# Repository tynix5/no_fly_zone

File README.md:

# no_fly_zone
A custom designed quadcopter and remote combination featuring a custom STM32-based flight controller PCB and STM32-based remote control PCB that combine aspects of sensor fusion, quaternion-based attitude control, wireless communication, and digital ESC communication.

<p align="center">
  <br>
  <em>Fully-assembled quadcopter</em>
</p>

<p align="center">
  <br>
  <em>Flight controller pictured with ESC mounted underneath</em>
</p>

<p align="center">
  <br>
  <em>Custom flight controller PCB</em>
</p>

<p align="center">
  <br>
  <em>Custom remote control frame</em>
</p>

<p align="center">
  <br>
  <em>Remote control PCB</em>
</p>

## Overview
This project focused on the design and implementation of a custom quadcopter flight controller paired with a complementary custom remote from the ground-up. Rather than buying an off-the-shelf flight controller and remote, almost all aspects of both the flight controller and remote were custom made. I decided to do this project because I have always been fascinated by drones, and I liked the challenge it would bring. It ties together all aspects of signal integrity, systems, low-level firmware, and digital signal processing. Below is a summary of some of the aspects this project entailed...

### Custom Features
- Flight controller PCB
- Remote control PCB
- Remote control frame
- Sensor fusion firmware
- Wireless nRF24L01 driver and handler
- Digital ESC communication implementation (DShot)
- Sensor libraries (IMU, Barometer, etc.)
- Encoder and OLED display libraries for remote control

No off-the-shelf software or firmware was used, but some aspects of flight controller design were inspired by PixHawk and Betaflight. Components purchased off-shelf include the ESC, four BLDC motors, quadcopter frame, and board components.

## Folder Overview
### /firmware
Contains source code, build settings, documentation, and additional information/diagrams for both the remote and quadcopter. A link to the STM32 submodule library can also be found, where most of the sensor implementation is found.

Note: The scripts subfolder in /firmware contains AI-generated Python scripts for validation and testing purposes. AI was NOT used to generate code found on either the remote or flight controller.

### /hardware
Contains KiCAD schematics and and PCB fabrication outputs for both the remote and quadcopter. Additional information on hardware selection and design can be found in each respective subfolder.

### /3d
Contains the 3D files for the spacers used to separate the STM32 flight controller board and ESC board, along with the 3D files for the remote control housing.

### /screenshots
Contains relevant screenshots for those in other READMEs

## BOM
All components purchased off-shelf can be found in the `bom.txt` file, and the BOMs for the PCBs can be found in the `.csv` files in their respective folders.

## Improvements
- Use of magnetometer or GPS unit for absolute heading
- Use of barometer for altitude hold
- Improved remote control PCB including nonvolatile storage (for PID parameters) and amplified transmission power
- Newer remote frame design

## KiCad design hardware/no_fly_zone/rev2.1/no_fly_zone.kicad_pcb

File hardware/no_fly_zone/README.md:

# no_fly_zone Schematic + PCB
## Overview

<p align="center">
  <br>
  <em>Flight controller PCBs. From left to right: Revision 1.0, 2.0, 2.1</em>
</p>

### Microcontroller
The MCU chosen was the STM32F446RCT for its high maximum clock frequency, dedicated FPU (for quaternion calculations), and abundant peripherals (SPI, timers, etc.). 
### IMU/Sensor Suite
The sensor suite in Revision 1.0 consists of a 6DOF IMU, magnetometer, barometer, and GPS. The IMU provides information on pitch and roll, magnetometer on yaw, barometer on altitude, and GPS for extended yaw support as well as location tracking for future revisions. Onboard magnetometers are very susceptible to EMF fields from motors, other sensors, as well as PCB traces. Thus, the GPS can be used as a backup for heading. Each subsequent iteration of the PCB reduced the sensors complexity until only the IMU and (optional) barometer remained. The GPS was removed for size and complexity reasons, and the magnetometer was removed due to the reasons described above. 
### Radio Communication
The nRF24L01 was the chosen RF link between the flight controller and remote for availablity and simplicity of implementation. In the future, a dedicated PA + LNA chip may be added on board to extend quadcopter range.
### Power Regulation
The power regulation circuit regulates the battery voltage (~16.8V) down to a smooth 5V, using a buck converter, then down to 3.3V, using an LDO, for powering the flight controller.

## Revision 1.0
### Summary

The single schematic given here is separated into two boards. A singular board containing all components was not able to fit onto the quadcopter frame. Thus, a separate MCU board and sensor board were produced using KiKit and connectors were used to share power and communication.

### Schematics

#### Hierarchal Schematic
The hierarchal schematic provides a top-level overview of the two boards. The ESC connectors, power schematic, and RF schematic were all included on the MCU board. The sensor board contains only the sensor schematic.

#### MCU

#### Sensors

#### Power

#### RF
Like the RF section on the remote, the nRF24L01 is surrounded by a continuous ground plane on the top layer as well as the layer directly underneath the antenna for stability. Stitching vias are placed about ~6mm apart (between lambda/10 - lambda/20 of 2.4 GHz wavelength) near antenna for shielding.

#### Misc
Contains 8 M3 screw holes, 4 for each board. Not shown for brevity.

#### PCB

#### 3D

## Revision 2.0
### Summary 
This revision involved consolidating the sensor board and MCU and removing the onboard magnetometer and GPS. The goal of this project was to achieve simple flight manuevers and hovering, and using these sensors would require more in depth sensor fusion algorithms. The antenna section was improved with further RF shielding and stitching vias, as well as a taper from the RF unbalanced port to the SMA pad. The board stackup changed from SIG - GND - 3.3V - SIG to a SIG - GND - GND - SIG + 3.3V to reduce buck converter and RF noise. 

Revision 1.0 board worked, but there were some problems with the JST connectors, making it hard to keep communication with the sensors, and they would not have been very reliable in a noisy and harsh environment. Ground lines were needed next to every signal line, but only one ground line was used on the entire board (power connector).

### Changes
- Consolidated sensor and controller board
- Removed magnetometer and GPS
- Improved RF shielding and layout
- Layer stackup changed from SIG-GND-3.3V-SIG to SIG-GND-GND-3.3V

### Schematics

### Hierarchal Schematic

#### MCU

#### Sensors

#### Power

#### RF

#### PCB

#### 3D

## Revision 2.1

### Summary 
While working with the Revision 2.0 flight controller, it was too large to fit comfortably on the quadcopter frame, so changes were made to reduce size while keeping functionality

### Changes
- Board size reduced from 50mm x 50mm to 40mm x 40mm
- Most part footprints reduced from 0805 packages to 0603
- Added TVS diodes to power inputs and connectors
- Removed ferrite bead in series with RF power supply
- Changed debug connector to STLINK specific
- Moved STAT3 from PB2 to PB8

#### MCU

#### Sensors

#### Power

#### RF

#### 3D

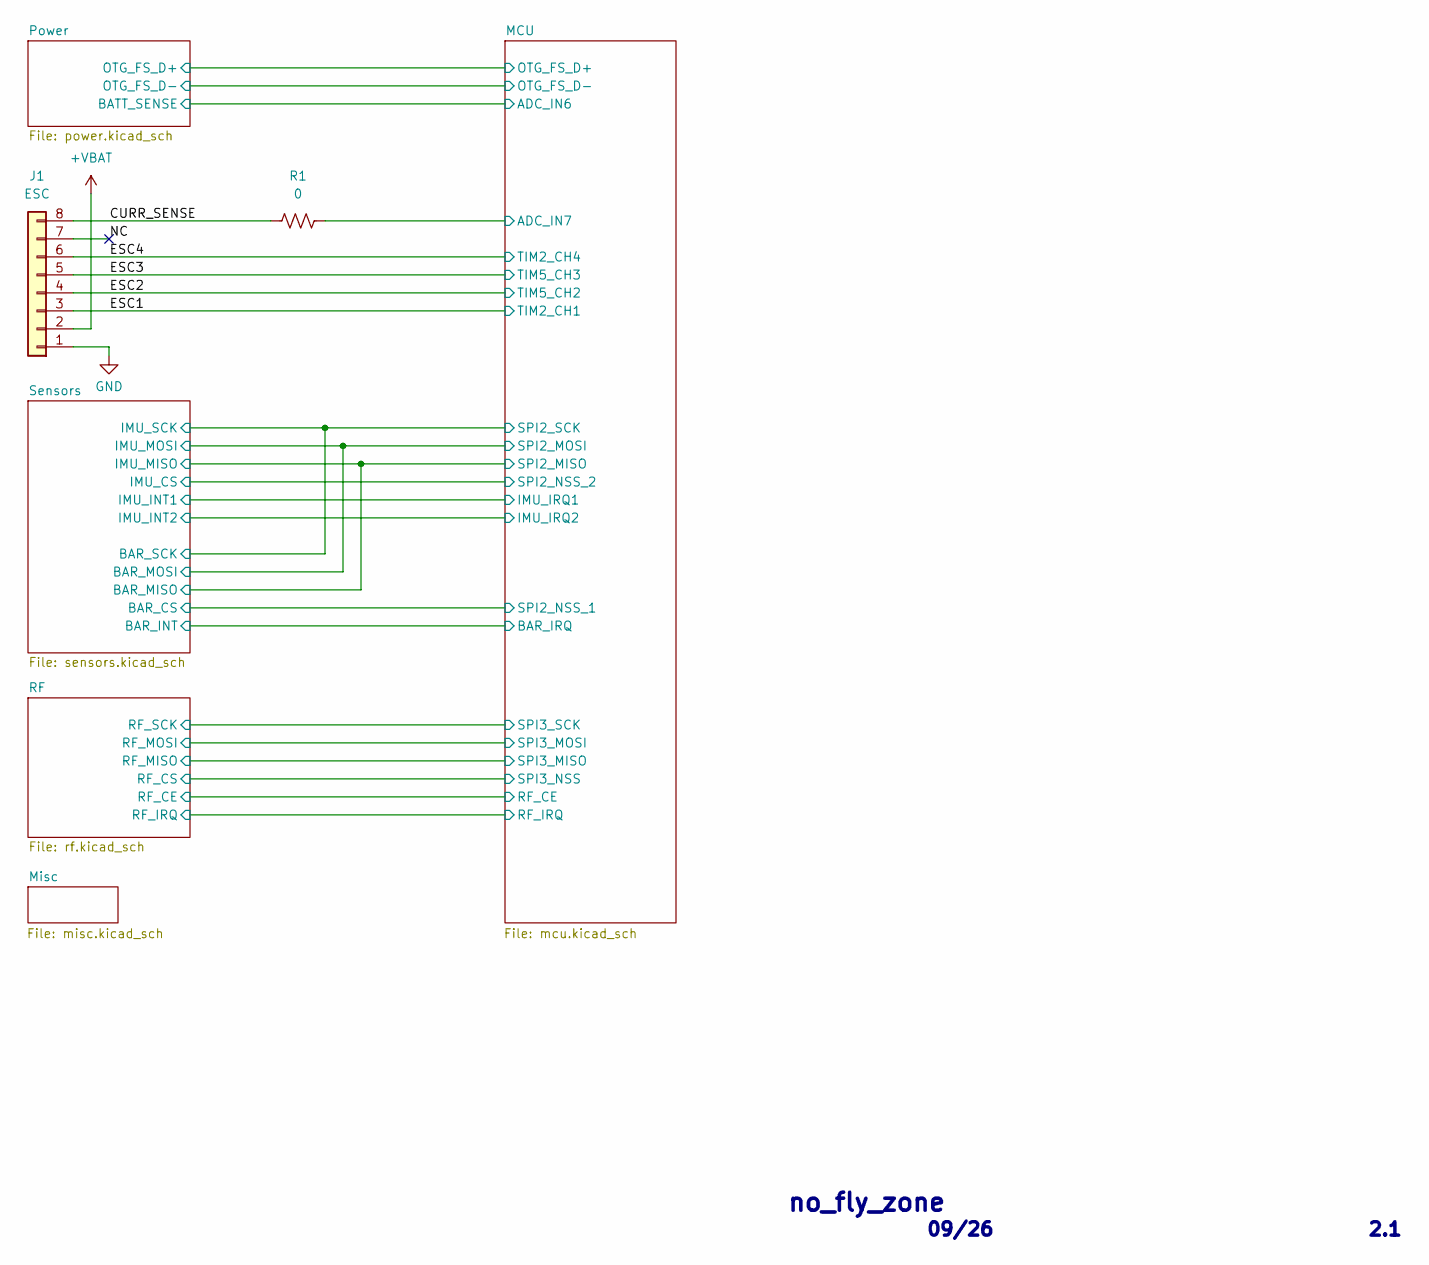
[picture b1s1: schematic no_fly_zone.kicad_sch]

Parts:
J1: ESC; JST_SH_SM08B-SRSS-TB_1x08-1MP_P1.00mm_Horizontal
R1: 0; R_0603_1608Metric

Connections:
+VBAT: J1.2; also elsewhere on the board
/CURR_SENSE: J1.8, R1.1
/ESC1: J1.3; also elsewhere on the board
/ESC2: J1.4; also elsewhere on the board
/ESC3: J1.5; also elsewhere on the board
/ESC4: J1.6; also elsewhere on the board
/MCU/ADC_IN7: R1.2; also elsewhere on the board
/NC: J1.7
GND: J1.1; also elsewhere on the board

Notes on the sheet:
no_fly_zone
2.1
09/26

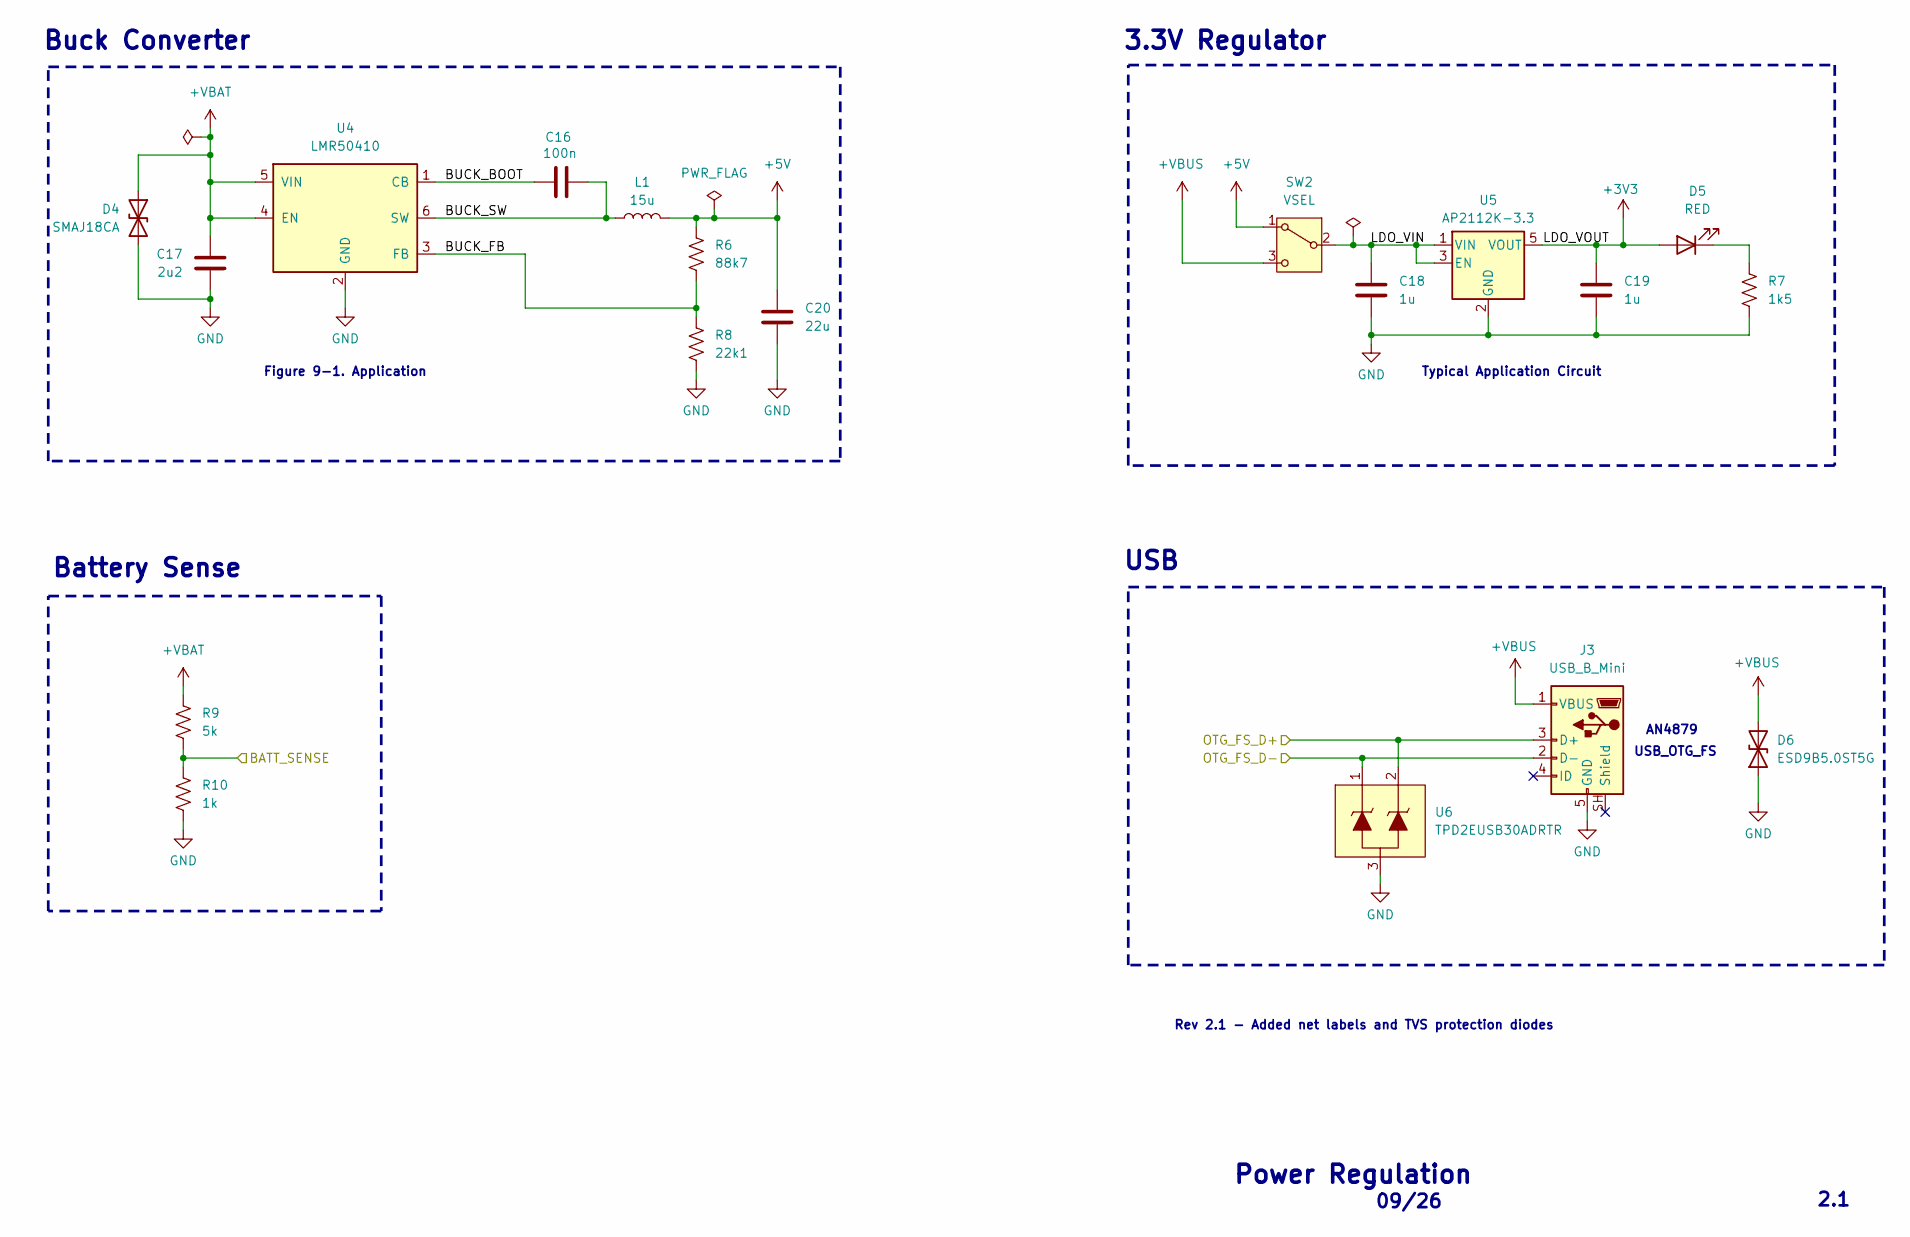
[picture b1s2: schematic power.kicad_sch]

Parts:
C16: 100n; C_0603_1608Metric
C17: 2u2; C_0603_1608Metric
C18, C19: 1u; C_0603_1608Metric
C20: 22u; C_0805_2012Metric
D4: SMAJ18CA; D_SMA
D5: RED; LED_0603_1608Metric
D6: ESD9B5.0ST5G; D_SOD-923
J3: USB_B_Mini; EDAC_690-005-299-043
L1: 15u; L_0805_2012Metric
R6: 88k7; R_0805_2012Metric
R7: 1k5; R_0603_1608Metric
R8: 22k1; R_0805_2012Metric
R9: 5k; R_0805_2012Metric
R10: 1k; R_0805_2012Metric
SW2: VSEL; SW_SPDT_PCM12
U4: LMR50410; SOT-23-6
U5: AP2112K-3.3; SOT-23-5
U6: SOT-723

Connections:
+3V3: C19.1, D5.2 (A), U5.5 (VOUT); also elsewhere on the board
+5V: C20.1, L1.2, R6.1, SW2.1 (A)
+VBAT: C17.1, D4.1 (A1), R9.1, U4.4 (EN), U4.5 (VIN); also elsewhere on the board
+VBUS: D6.2 (A2), J3.1 (VBUS), SW2.3 (C)
/MCU/ADC_IN6: R9.2, R10.1; also elsewhere on the board
/MCU/OTG_FS_D+: J3.3 (D+), U6.2; also elsewhere on the board
/MCU/OTG_FS_D-: J3.2 (D-), U6.1; also elsewhere on the board
/Power/BUCK_BOOT: C16.1, U4.1 (CB)
/Power/BUCK_FB: R6.2, R8.1, U4.3 (FB)
/Power/BUCK_SW: C16.2, L1.1, U4.6 (SW)
/Power/LDO_VIN: C18.1, SW2.2 (B), U5.1 (VIN), U5.3 (EN)
GND: C17.2, C18.2, C19.2, C20.2, D4.2 (A2), D6.1 (A1), J3.5 (GND), R7.2, R8.2, R10.2, U4.2 (GND), U5.2 (GND), U6.3; also elsewhere on the board
unnamed: D5.1 (K), R7.1

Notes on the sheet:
USB
Figure 9-1. Application
USB_OTG_FS
09/26
AN4879
Buck Converter
Power Regulation
3.3V Regulator
Rev 2.1 - Added net labels and TVS protection diodes
2.1
Battery Sense
Typical Application Circuit

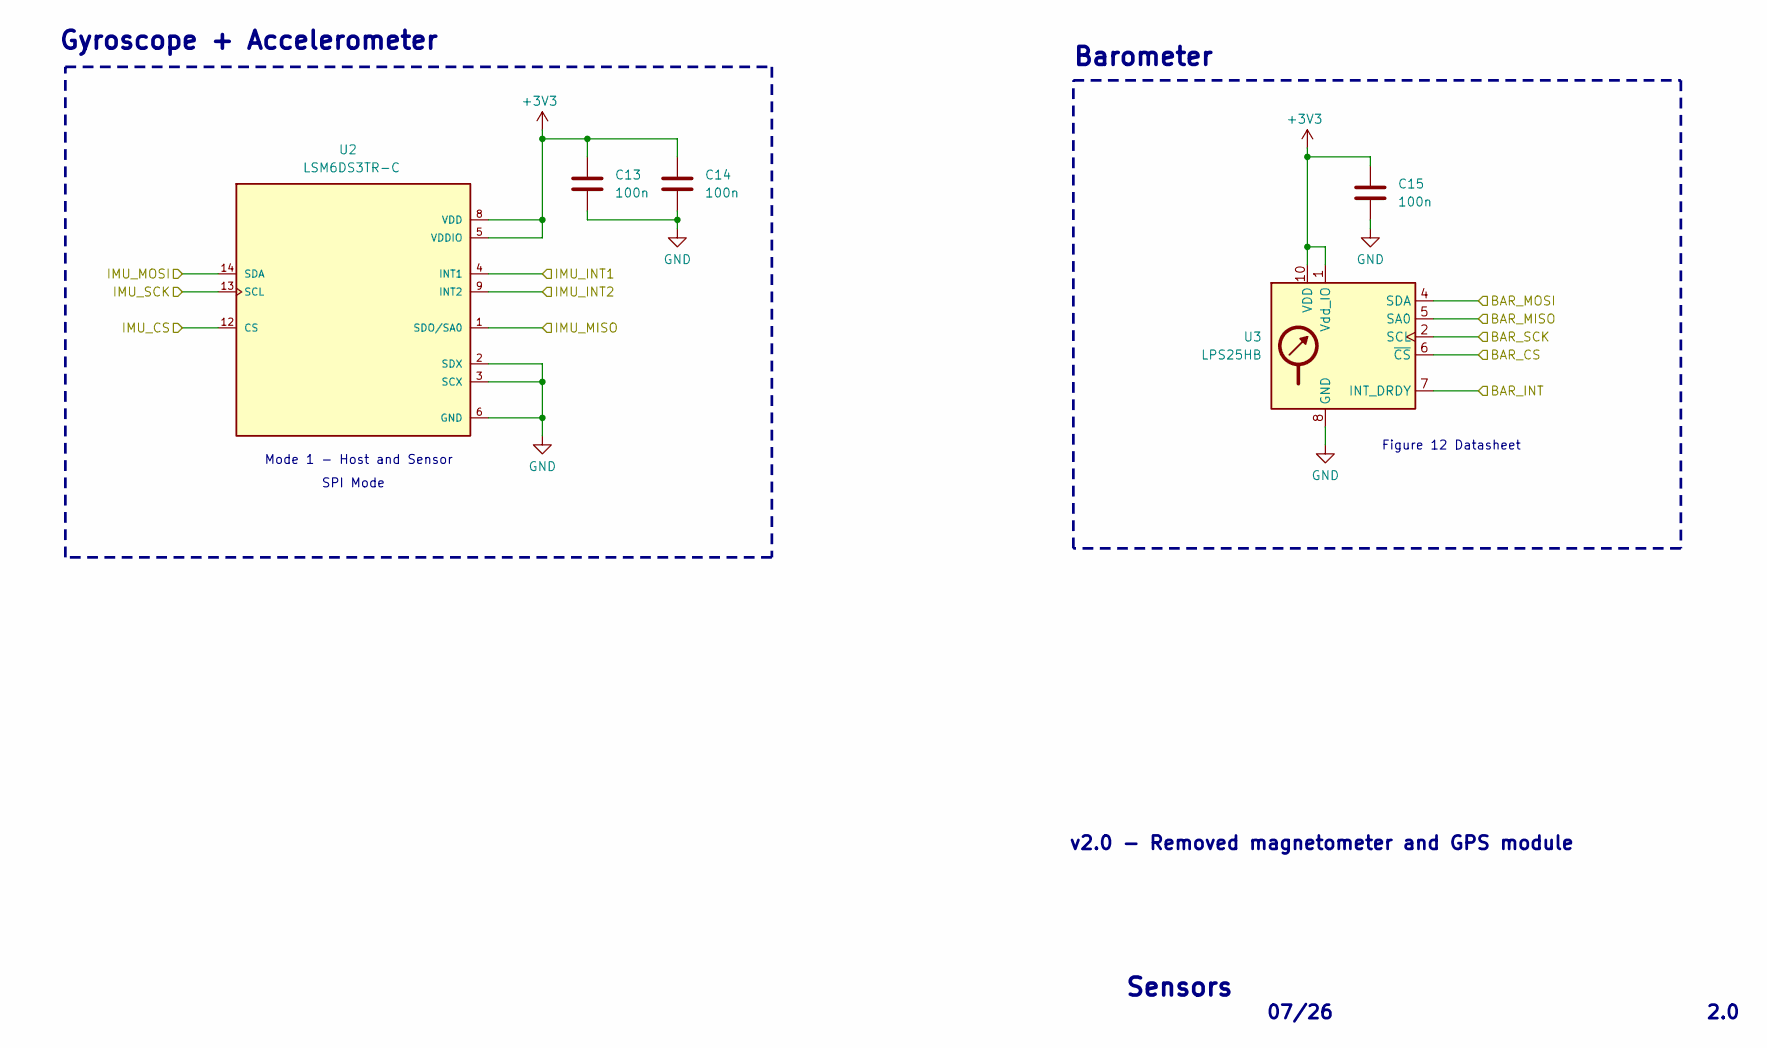
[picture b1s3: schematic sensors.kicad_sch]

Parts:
C13, C14, C15: 100n; C_0603_1608Metric
U2: LSM6DS3TR-C; LSM6DS3TR
U3: LPS25HB; ST_HLGA-10_2.5x2.5mm_P0.6mm_LayoutBorder3x2y

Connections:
+3V3: C13.1, C14.1, C15.1, U2.5 (VDDIO), U2.8 (VDD), U3.1 (Vdd_IO), U3.10 (VDD); also elsewhere on the board
/MCU/BAR_IRQ: U3.7 (INT_DRDY); also elsewhere on the board
/MCU/IMU_IRQ1: U2.4 (INT1); also elsewhere on the board
/MCU/IMU_IRQ2: U2.9 (INT2); also elsewhere on the board
/MCU/SPI2_MISO: U2.1 (SDO/SA0), U3.5 (SA0); also elsewhere on the board
/MCU/SPI2_MOSI: U2.14 (SDA), U3.4 (SDA); also elsewhere on the board
/MCU/SPI2_NSS_1: U3.6 (~CS); also elsewhere on the board
/MCU/SPI2_NSS_2: U2.12 (CS); also elsewhere on the board
/MCU/SPI2_SCK: U2.13 (SCL), U3.2 (SCL); also elsewhere on the board
GND: C13.2, C14.2, C15.2, U2.2 (SDX), U2.3 (SCX), U2.6 (GND), U2.7 (GND), U3.3 (GND), U3.8 (GND), U3.9 (GND); also elsewhere on the board

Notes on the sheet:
SPI Mode
Barometer
07/26
Mode 1 - Host and Sensor
2.0
Gyroscope + Accelerometer
Figure 12 Datasheet
v2.0 - Removed magnetometer and GPS module
Sensors

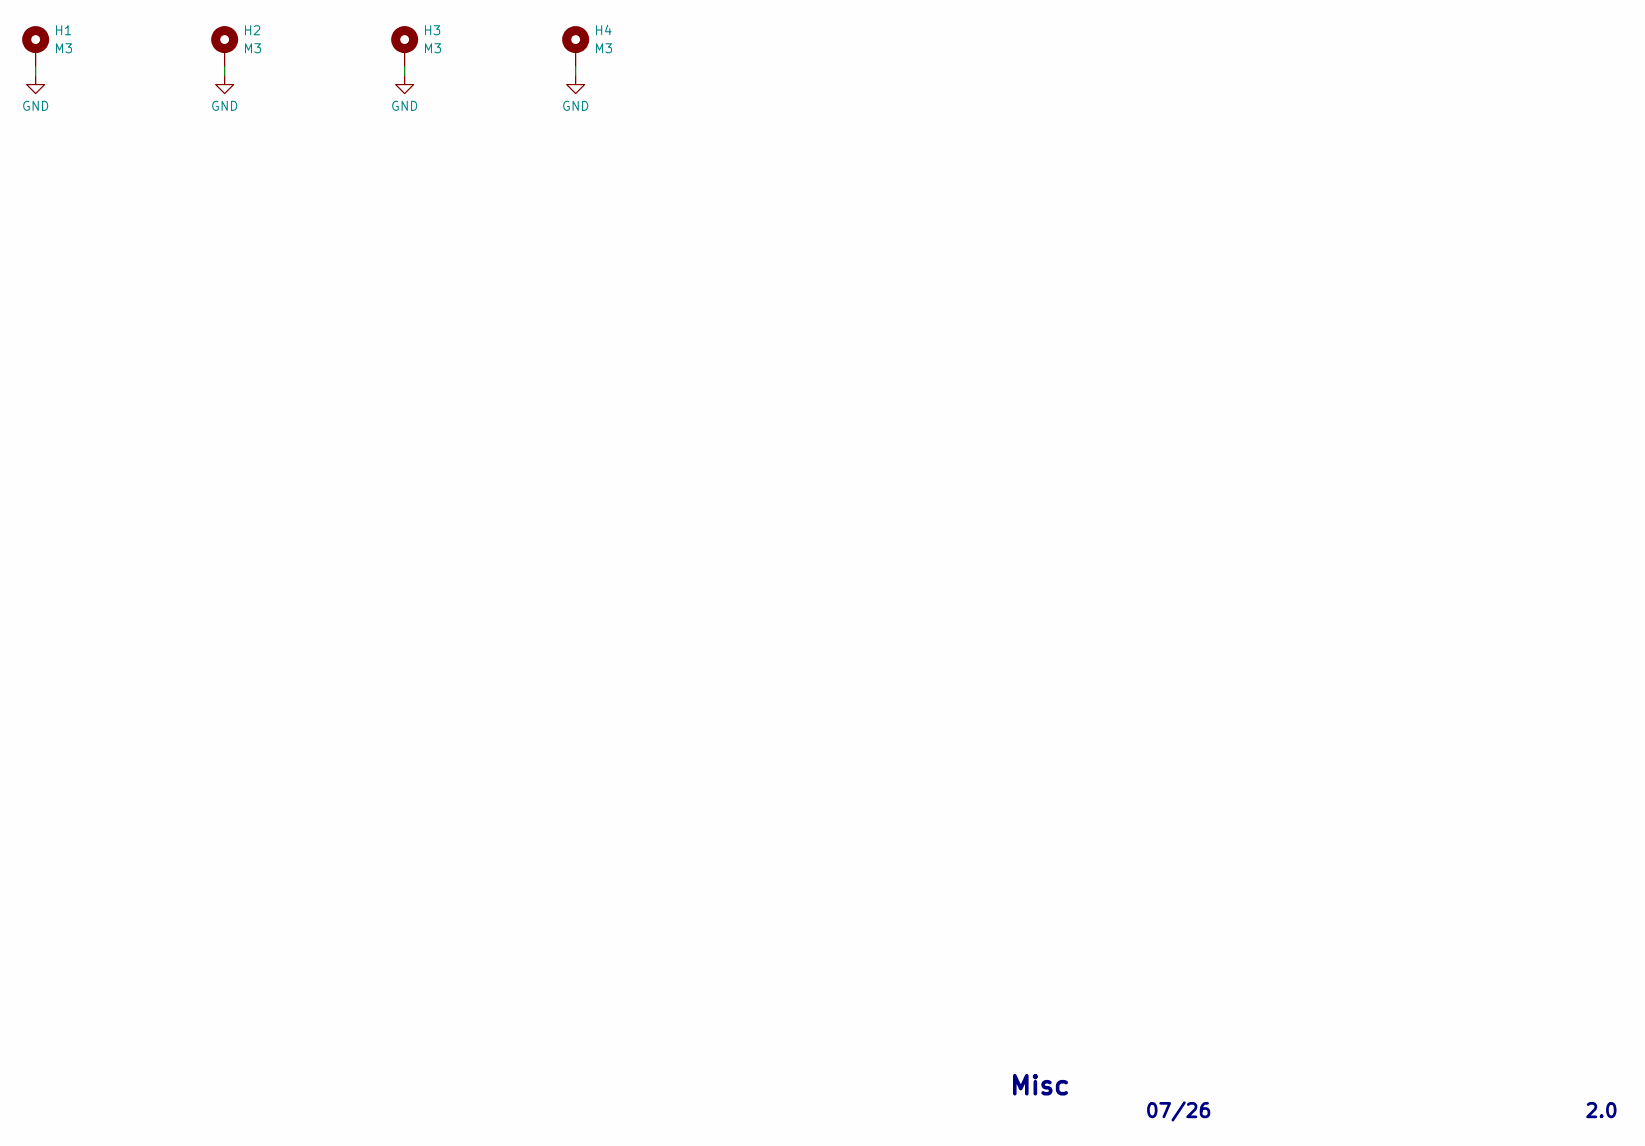
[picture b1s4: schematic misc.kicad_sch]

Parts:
H1, H2, H3, H4: M3; MountingHole_3.2mm_M3_DIN965_Pad

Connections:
GND: H1.1 (1_1), H2.1 (1_1), H3.1 (1_1), H4.1 (1_1); also elsewhere on the board

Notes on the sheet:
07/26
2.0
Misc

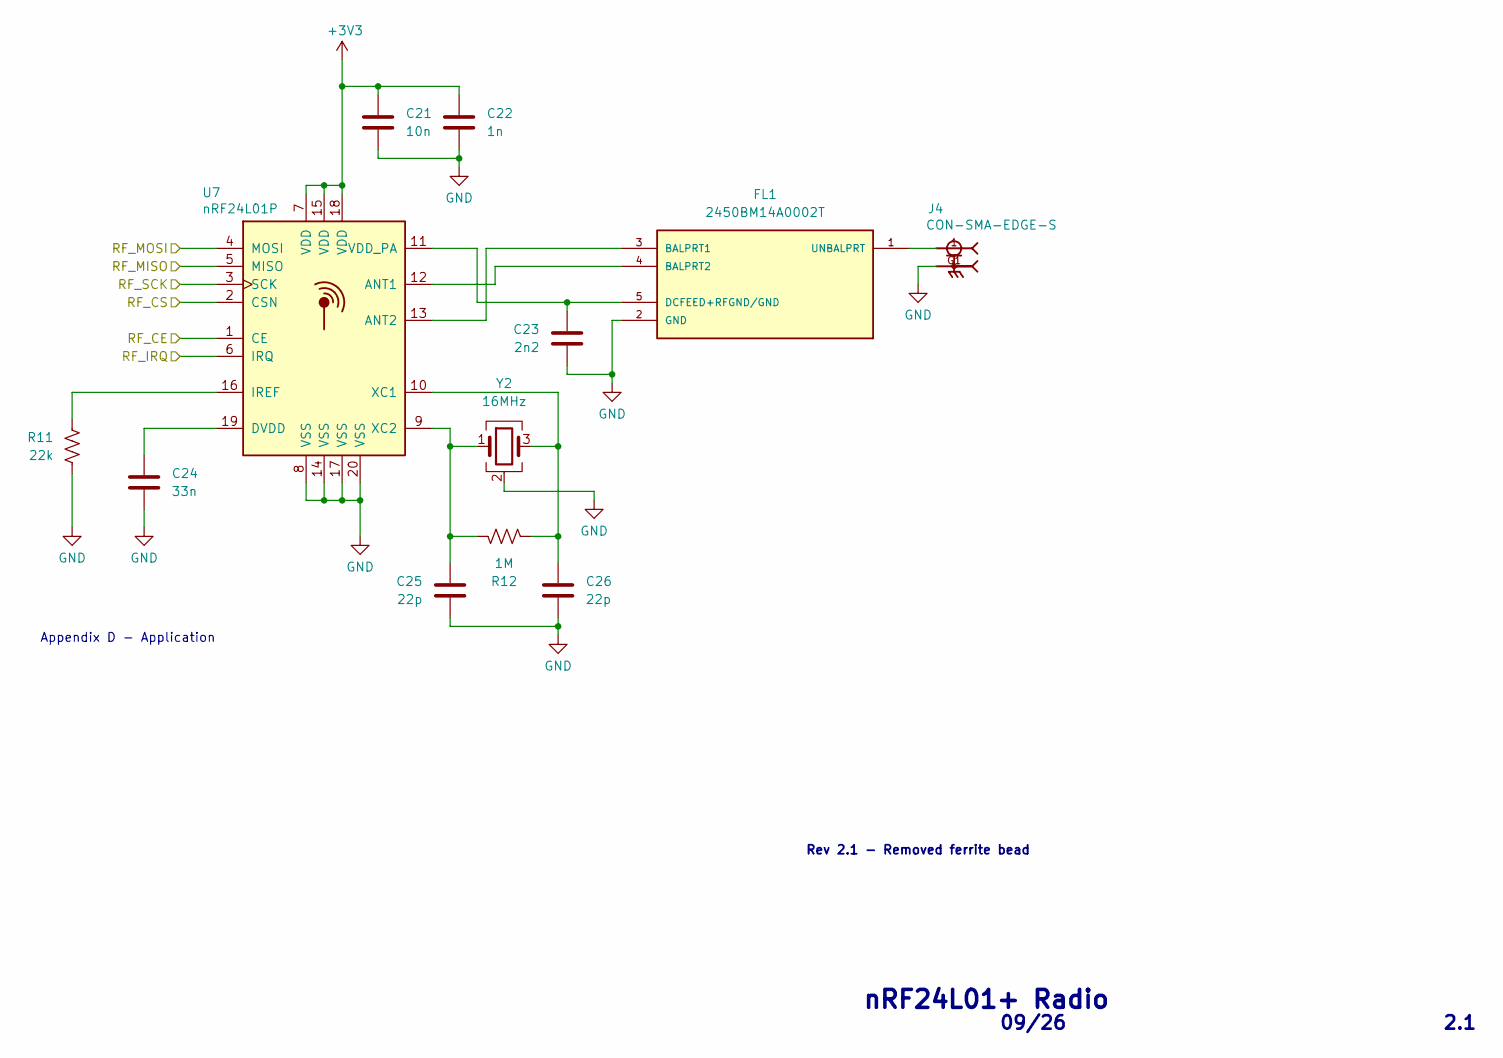
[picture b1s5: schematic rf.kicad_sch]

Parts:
C21: 10n; C_0402_1005Metric
C22: 1n; C_0402_1005Metric
C23: 2n2; C_0402_1005Metric
C24: 33n; C_0402_1005Metric
C25, C26: 22p; C_0402_1005Metric
FL1: 2450BM14A0002T; FIL_2450BM14A0002T
J4: CON-SMA-EDGE-S; RFSOLUTIONS_CON-SMA-EDGE-S
R11: 22k; R_0402_1005Metric
R12: 1M; R_0402_1005Metric
U7: nRF24L01P; QFN-20-1EP_4x4mm_P0.5mm_EP2.5x2.5mm
Y2: 16MHz; XTAL_ABM8AIG-16.000MHZ-12-2Z-T3

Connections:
+3V3: C21.1, C22.1, U7.7 (VDD), U7.15 (VDD), U7.18 (VDD); also elsewhere on the board
/MCU/RF_CE: U7.1 (CE); also elsewhere on the board
/MCU/RF_IRQ: U7.6 (IRQ); also elsewhere on the board
/MCU/SPI3_MISO: U7.5 (MISO); also elsewhere on the board
/MCU/SPI3_MOSI: U7.4 (MOSI); also elsewhere on the board
/MCU/SPI3_NSS: U7.2 (CSN); also elsewhere on the board
/MCU/SPI3_SCK: U7.3 (SCK); also elsewhere on the board
GND: C21.2, C22.2, C23.2, C24.2, C25.2, C26.2, FL1.2 (GND), J4.G1, J4.G2, J4.G3, J4.G4, R11.2, U7.8 (VSS), U7.14 (VSS), U7.17 (VSS), U7.20 (VSS), Y2.2 (G), Y2.4 (G); also elsewhere on the board
unnamed: FL1.3 (BALPRT1), U7.13 (ANT2)
unnamed: FL1.4 (BALPRT2), U7.12 (ANT1)
unnamed: C23.1, FL1.5 (DCFEED+RFGND/GND), U7.11 (VDD_PA)
unnamed: FL1.1 (UNBALPRT), J4.1
unnamed: C24.1, U7.19 (DVDD)
unnamed: R11.1, U7.16 (IREF)
unnamed: C26.1, R12.1, U7.10 (XC1), Y2.3
unnamed: C25.1, R12.2, U7.9 (XC2), Y2.1

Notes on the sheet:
Appendix D - Application
Rev 2.1 - Removed ferrite bead
2.1
nRF24L01+ Radio
09/26

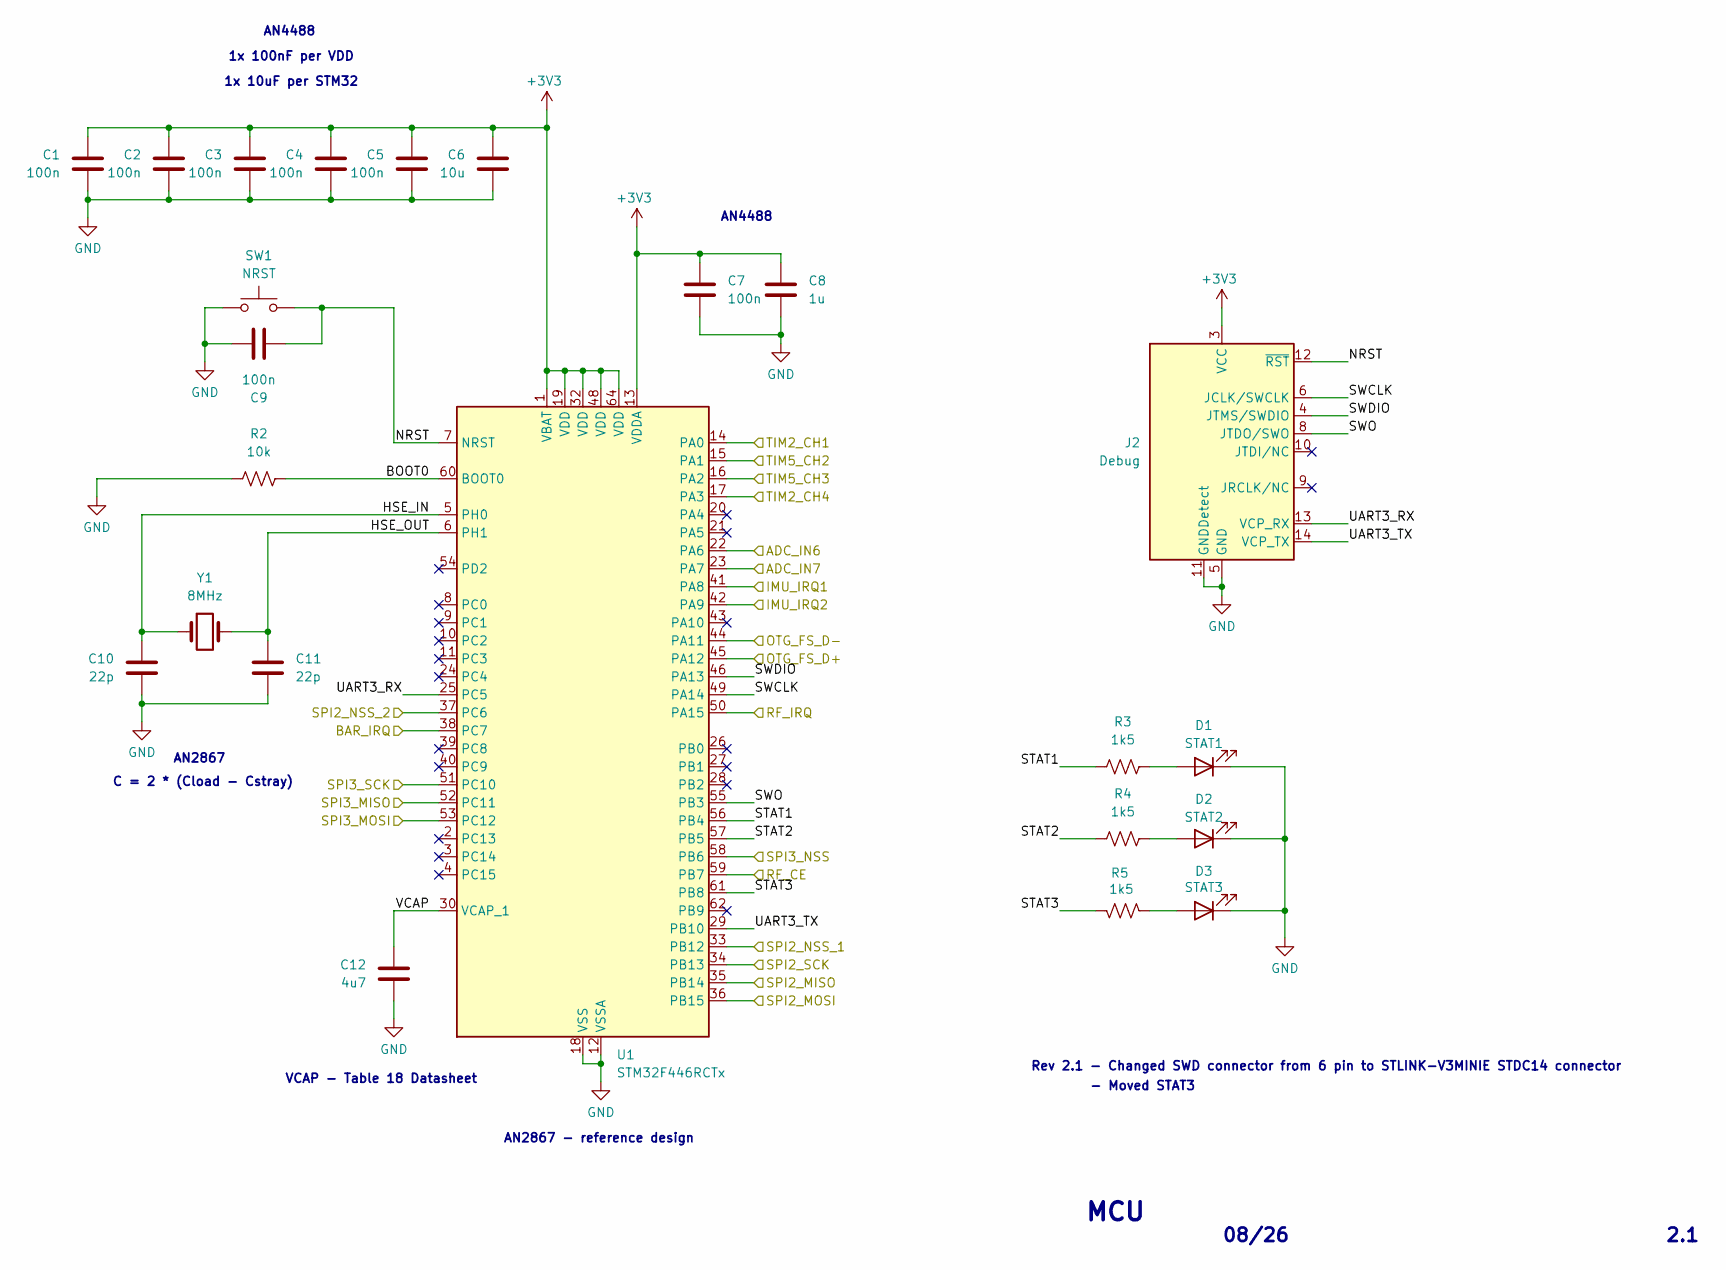
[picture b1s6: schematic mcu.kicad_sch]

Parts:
C1, C2, C3, C4, C5, C7, C9: 100n; C_0603_1608Metric
C6: 10u; C_0603_1608Metric
C8: 1u; C_0603_1608Metric
C10, C11: 22p; C_0603_1608Metric
C12: 4u7; C_0603_1608Metric
D1: STAT1; LED_0603_1608Metric
D2: STAT2; LED_0603_1608Metric
D3: STAT3; LED_0603_1608Metric
J2: Debug; SAMTEC_FTSH-107-01-L-DV-K-A
R2: 10k; R_0603_1608Metric
R3, R4, R5: 1k5; R_0603_1608Metric
SW1: NRST; SW_SPST_TL3305A
U1: STM32F446RCTx; LQFP-64_10x10mm_P0.5mm
Y1: 8MHz; XTAL_ABM3-16.000MHZ-D2Y-T

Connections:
+3V3: C1.1, C2.1, C3.1, C4.1, C5.1, C6.1, C7.1, C8.1, J2.3 (VCC), U1.1 (VBAT), U1.13 (VDDA), U1.19 (VDD), U1.32 (VDD), U1.48 (VDD), U1.64 (VDD); also elsewhere on the board
/ESC1: U1.14 (PA0); also elsewhere on the board
/ESC2: U1.15 (PA1); also elsewhere on the board
/ESC3: U1.16 (PA2); also elsewhere on the board
/ESC4: U1.17 (PA3); also elsewhere on the board
/MCU/ADC_IN6: U1.22 (PA6); also elsewhere on the board
/MCU/ADC_IN7: U1.23 (PA7); also elsewhere on the board
/MCU/BAR_IRQ: U1.38 (PC7); also elsewhere on the board
/MCU/BOOT0: R2.2, U1.60 (BOOT0)
/MCU/HSE_IN: C10.1, U1.5 (PH0), Y1.1
/MCU/HSE_OUT: C11.1, U1.6 (PH1), Y1.2
/MCU/IMU_IRQ1: U1.41 (PA8); also elsewhere on the board
/MCU/IMU_IRQ2: U1.42 (PA9); also elsewhere on the board
/MCU/NRST: C9.1, J2.12 (~RST), SW1.2, U1.7 (NRST)
/MCU/OTG_FS_D+: U1.45 (PA12); also elsewhere on the board
/MCU/OTG_FS_D-: U1.44 (PA11); also elsewhere on the board
/MCU/RF_CE: U1.59 (PB7); also elsewhere on the board
/MCU/RF_IRQ: U1.50 (PA15); also elsewhere on the board
/MCU/SPI2_MISO: U1.35 (PB14); also elsewhere on the board
/MCU/SPI2_MOSI: U1.36 (PB15); also elsewhere on the board
/MCU/SPI2_NSS_1: U1.33 (PB12); also elsewhere on the board
/MCU/SPI2_NSS_2: U1.37 (PC6); also elsewhere on the board
/MCU/SPI2_SCK: U1.34 (PB13); also elsewhere on the board
/MCU/SPI3_MISO: U1.52 (PC11); also elsewhere on the board
/MCU/SPI3_MOSI: U1.53 (PC12); also elsewhere on the board
/MCU/SPI3_NSS: U1.58 (PB6); also elsewhere on the board
/MCU/SPI3_SCK: U1.51 (PC10); also elsewhere on the board
/MCU/STAT1: R3.1, U1.56 (PB4)
/MCU/STAT2: R4.1, U1.57 (PB5)
/MCU/STAT3: R5.2, U1.61 (PB8)
/MCU/SWCLK: J2.6 (JCLK/SWCLK), U1.49 (PA14)
/MCU/SWDIO: J2.4 (JTMS/SWDIO), U1.46 (PA13)
/MCU/SWO: J2.8 (JTDO/SWO), U1.55 (PB3)
/MCU/UART3_RX: J2.13 (VCP_RX), U1.25 (PC5)
/MCU/UART3_TX: J2.14 (VCP_TX), U1.29 (PB10)
/MCU/VCAP: C12.1, U1.30 (VCAP_1)
GND: C1.2, C2.2, C3.2, C4.2, C5.2, C6.2, C7.2, C8.2, C9.2, C10.2, C11.2, C12.2, D1.1 (K), D2.1 (K), D3.1 (K), J2.5 (GND), J2.7 (GND), J2.11 (GNDDetect), R2.1, SW1.1, U1.12 (VSSA), U1.18 (VSS), U1.31 (VSS), U1.47 (VSS), U1.63 (VSS); also elsewhere on the board
unnamed: D1.2 (A), R3.2
unnamed: D2.2 (A), R4.2
unnamed: D3.2 (A), R5.1

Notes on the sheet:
AN4488
1x 100nF per VDD
2.1
MCU
08/26
- Moved STAT3
VCAP - Table 18 Datasheet
Rev 2.1 - Changed SWD connector from 6 pin to STLINK-V3MINIE STDC14 connector
AN2867 - reference design
1x 10uF per STM32
C = 2 * (Cload - Cstray)
AN2867

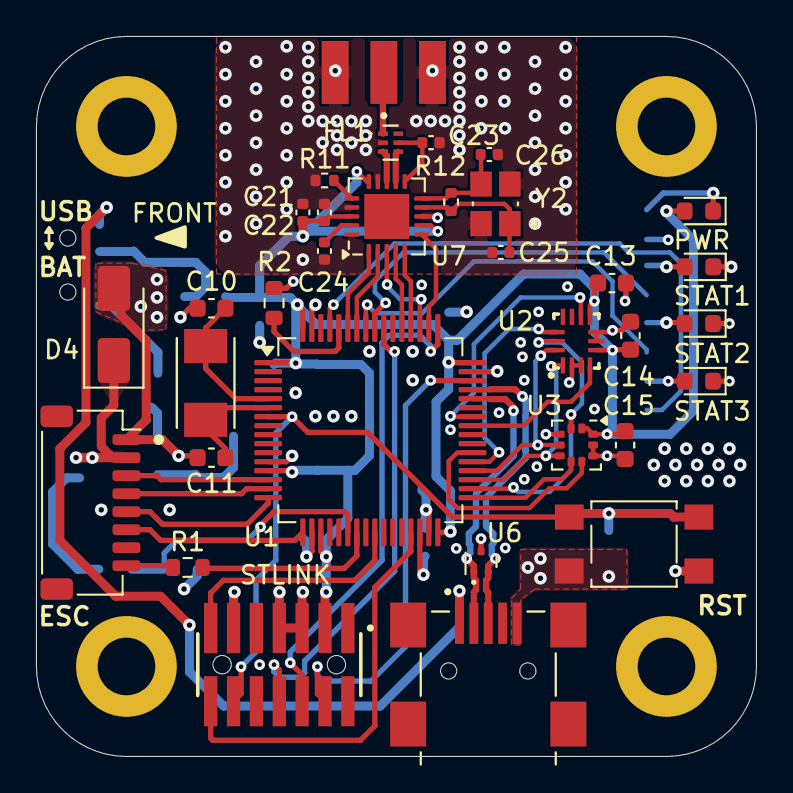
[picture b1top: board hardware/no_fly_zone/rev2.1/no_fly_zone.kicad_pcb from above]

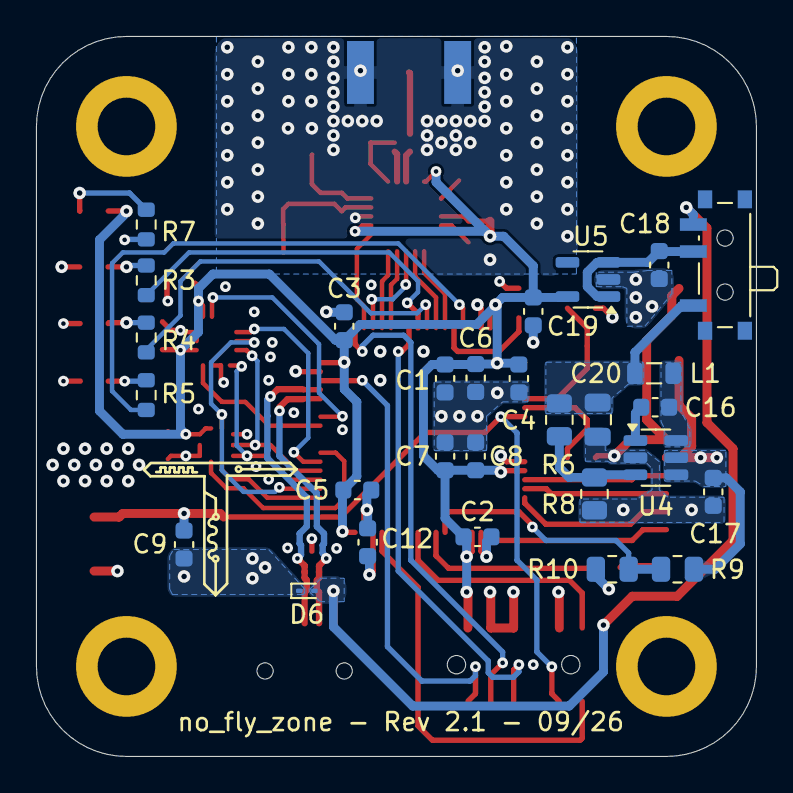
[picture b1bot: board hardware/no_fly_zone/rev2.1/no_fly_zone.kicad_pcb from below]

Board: 4 copper layers, 40.0 x 40.0 mm, 65 parts (28 on the bottom side), 57 nets.

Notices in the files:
firmware/no_fly_zone_remote/Core/Src/stm32l4xx_hal_msp.c:
Copyright (c) 2026 STMicroelectronics.
All rights reserved.
This software is licensed under terms that can be found in the LICENSE file
